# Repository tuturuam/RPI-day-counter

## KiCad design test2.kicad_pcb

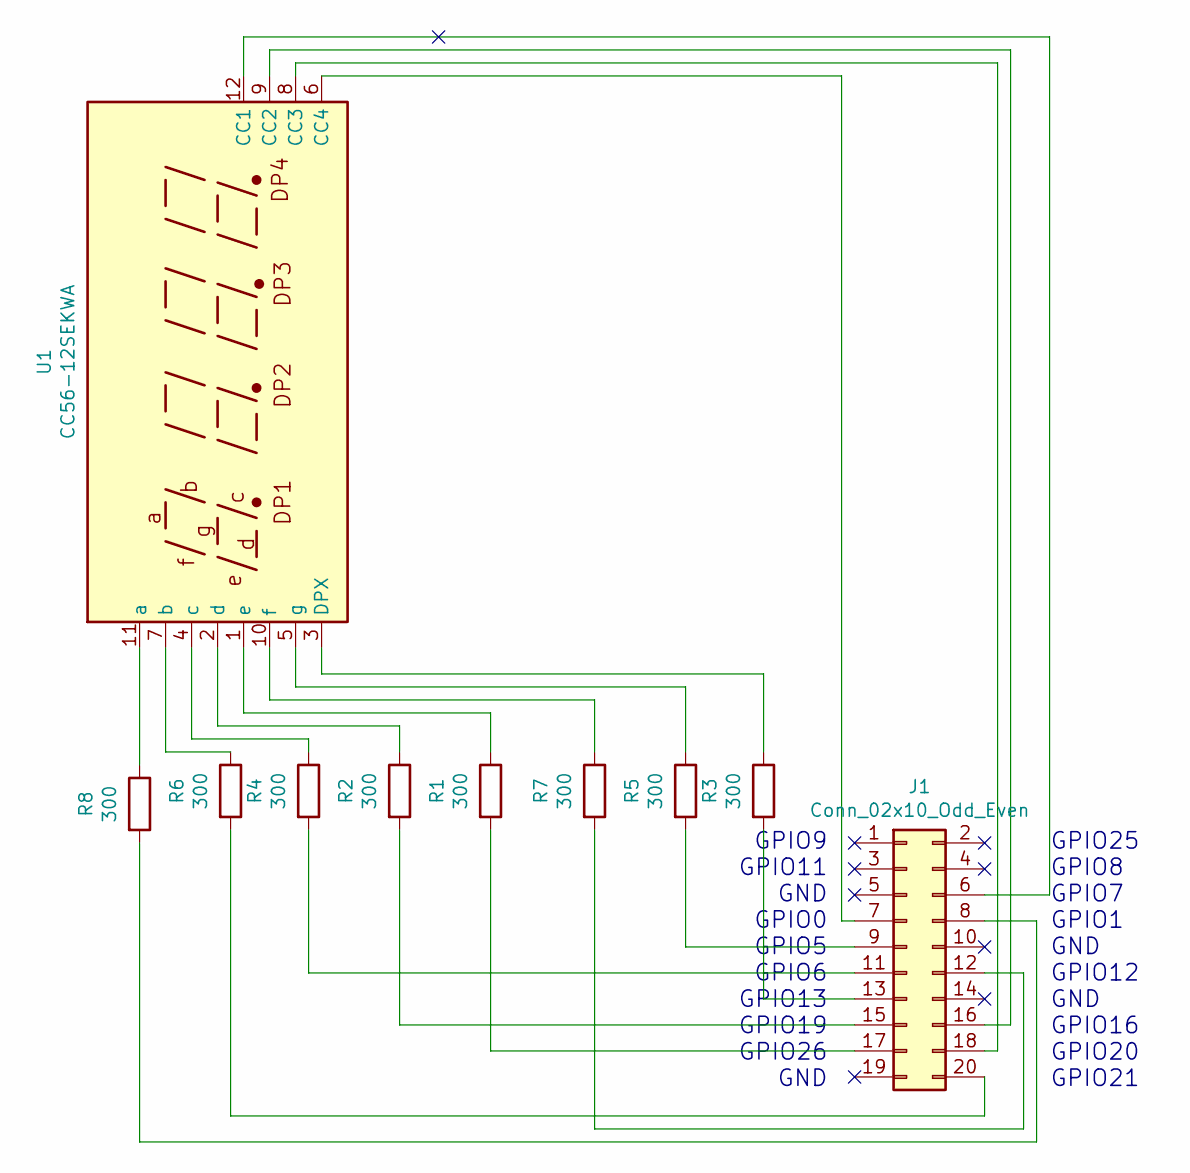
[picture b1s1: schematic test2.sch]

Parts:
J1: Conn_02x10_Odd_Even; PinHeader_2x10_P2.54mm_Vertical
R1, R2, R3, R4, R5, R6, R7, R8: 300; R_1206_3216Metric_Pad1.42x1.75mm_HandSolder
U1: CC56-12SEKWA; CA56-12SEKWA

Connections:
unnamed: J1.6, U1.12 (CC1)
unnamed: J1.7, U1.6 (CC4)
unnamed: J1.8, R8.2
unnamed: J1.9, R5.2
unnamed: J1.11, R4.2
unnamed: J1.12, R7.2
unnamed: J1.13, R3.2
unnamed: J1.15, R2.2
unnamed: J1.16, U1.9 (CC2)
unnamed: J1.17, R1.2
unnamed: J1.18, U1.8 (CC3)
unnamed: J1.20, R6.2
unnamed: R1.1, U1.1 (e)
unnamed: R2.1, U1.2 (d)
unnamed: R3.1, U1.3 (DPX)
unnamed: R4.1, U1.4 (c)
unnamed: R5.1, U1.5 (g)
unnamed: R6.1, U1.7 (b)
unnamed: R7.1, U1.10 (f)
unnamed: R8.1, U1.11 (a)

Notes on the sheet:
GPIO9 GPIO11 GND GPIO0 GPIO5 GPIO6 GPIO13 GPIO19 GPIO26 GND
GPIO25 GPIO8 GPIO7 GPIO1 GND GPIO12 GND GPIO16 GPIO20 GPIO21

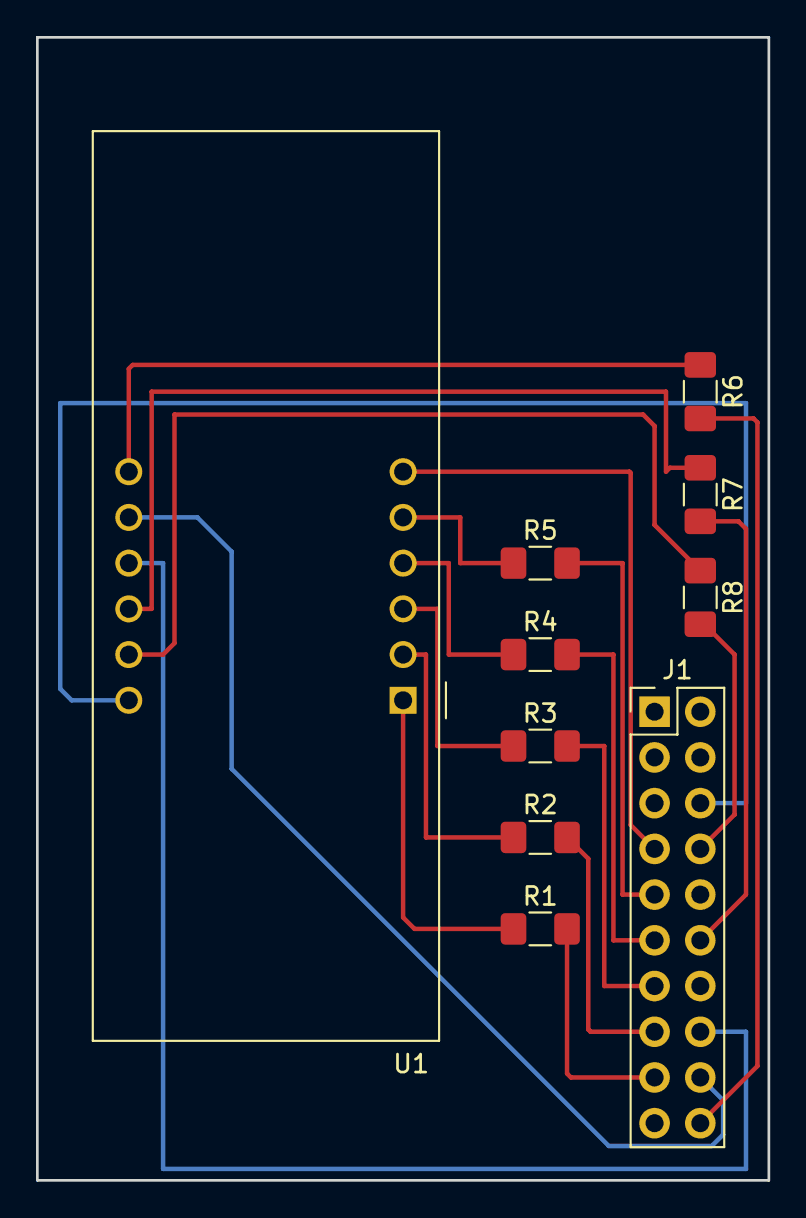
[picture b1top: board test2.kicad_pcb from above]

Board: 2 copper layers, 40.6 x 63.5 mm, 10 parts (0 on the bottom side), 20 nets.

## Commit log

2018-12-16 new file: README.md
2018-12-16 new kicad files
2018-12-17 new file: date_from.py new file: segment.py
